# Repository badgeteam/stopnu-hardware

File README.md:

# STOPNU traffic light controller board

## Introduction

The StopNU board is an interface board design to be used with an Heltec V3 board, with purpose to provide a LoRa synchronized traffic light system.
The board has the ability to process inputs from: an Ambient light sensor, 3 button IO channels, a QWIIC interface.
The board can control LED strips via 5V LED control output lines, and using QWIIC peripherals.
IO is also exposed to the 'Expansion connector', which provides a way to breakout IO to future boards.

## Power

The board will be provided 5V power, stabilized outside of the board.
Because the current consumption is limited to 1A, the board it self cannot provide power to LED's controlled by the board.

Even though 3.3V and 5V pins are provided with the expansion header, the total power of these two power railes combined is limited at 3W.

## Pin-out

### Ambient light sensor

The ambient light sensor this circuit is designed for is the [TEPT4400](https://www.vishay.com/docs/81341/tept4400.pdf), where the sensor is connected between the collector and emitter pin.
The current allowed through the sensor results in a voltage that needs to be decoded by the ESP32 micro controller ADC input pin.

The emitter is is connected to ADC pin GPIO02

### LED control outputs

The LED control output pins are level shifted to 5V TTL, in order to work with the WS2812 addressable LED's or compatible.
The pins are output only as the level shifter only works one way.

| LED output | GPIO   |
| ---------- | ------ |
| 1          | GPIO04 |
| 2          | GPIO03 |

### Digital input lines

In order for external input devices to work with the board, 3 input lines have been provided, that are routed through an opto-coupler in order to be more noise resistant.
The IO pins are pulled up to 5V, and need to be pulled down by the input device in order for the board to register an input.

When the pin is pulled down the current through the IO input is 5 mA.

| Button # | GPIO   |
| -------- | ------ |
| 1        | GPIO07 |
| 2        | GPIO06 |
| 3        | GPIO07 |

### QWIIC connector

The QWIIC connector is there to connect external I2C (IIC) sensors and IO modules to the board, providing an extra method of expansion.
The port complies with the pin out and specs as provided by [QWIIC Sparkfun page](https://www.sparkfun.com/qwiic), QWIIC products sold are compatible with this board.

Again for the QWIIC bus 3.3V power supply counts, 3W budget shared with the other peripherals on the board.

| QWIIC pin | GPIO   |
| --------- | -----  |
| SDA       | GPIO34 |
| SCL       | GPIO33 |

### Expansion connector

The expansion connector exposes the Heltec V3 pins useable for IO.
The pins that are connected to the buffered outputs on the bottom of the board are also exposed on the header, but without the buffering.

Please be aware that some pins exposed on the header are used by the Heltec V3 internally, and should be used with care.

Here a list of the Heltec V3 board pins and where they connect to on the expansion header.

| pin | GPIO    | capable        | comments                        |
| --- | ------- | -------------- | ------------------------------- |
| 1   | GND     | Power          |                                 |
| 2   | GND     | Power          |                                 |
| 3   | GPIO41  |                |                                 |
| 4   | GPIO44  |                | Heltec V3 UAR_TX                |
| 5   | GPIO40  |                | Drives Heltec white LED         |
| 6   | GPIO43  |                | Heltec V3 UART_RX               |
| 7   | GPIO39  |                | Heltec V3 external power switch |
| 8   | MCU_RST |                | Heltec V3 Reset pin             |
| 9   | GPIO38  |                | Heltec V3 ADC ctrl              |
| 10  | GPIO00  |                | USER_KEY                        |
| 11  | GPIO01  | ADC            |                                 |
| 12  | GPIO35  |                |                                 |
| 13  | GPIO02  | ADC            |                                 |
| 14  | GPIO34  |                | QWIIC SDA                       |
| 15  | +3.3V   | Power          | 3W max (total)                  |
| 16  | +5V     | Power          | 3W max (total)                  |
| 17  | GND     | Power          |                                 |
| 18  | GND     | Power          |                                 |
| 19  | GPIO03  | ADC            | LED channel 2                   |
| 20  | GPIO45  |                |                                 |
| 21  | GPIO04  | ADC            | LED channel 1                   |
| 22  | GPIO33  |                | QWIIC SCL                       |
| 23  | GPIO05  | ADC            | Button IN 3                     |
| 24  | GPIO46  |                |                                 |
| 25  | GPIO06  | ADC/Input only | Button IN 2                     |
| 26  | GPIO42  |                |
| 27  | GPIO07  | ADC/Input only | Button IN 1                     |
| 28  | GPIO26  |                |                                 |
| 29  | GND     | Power          |                                 |
| 30  | GND     | Power          |                                 |

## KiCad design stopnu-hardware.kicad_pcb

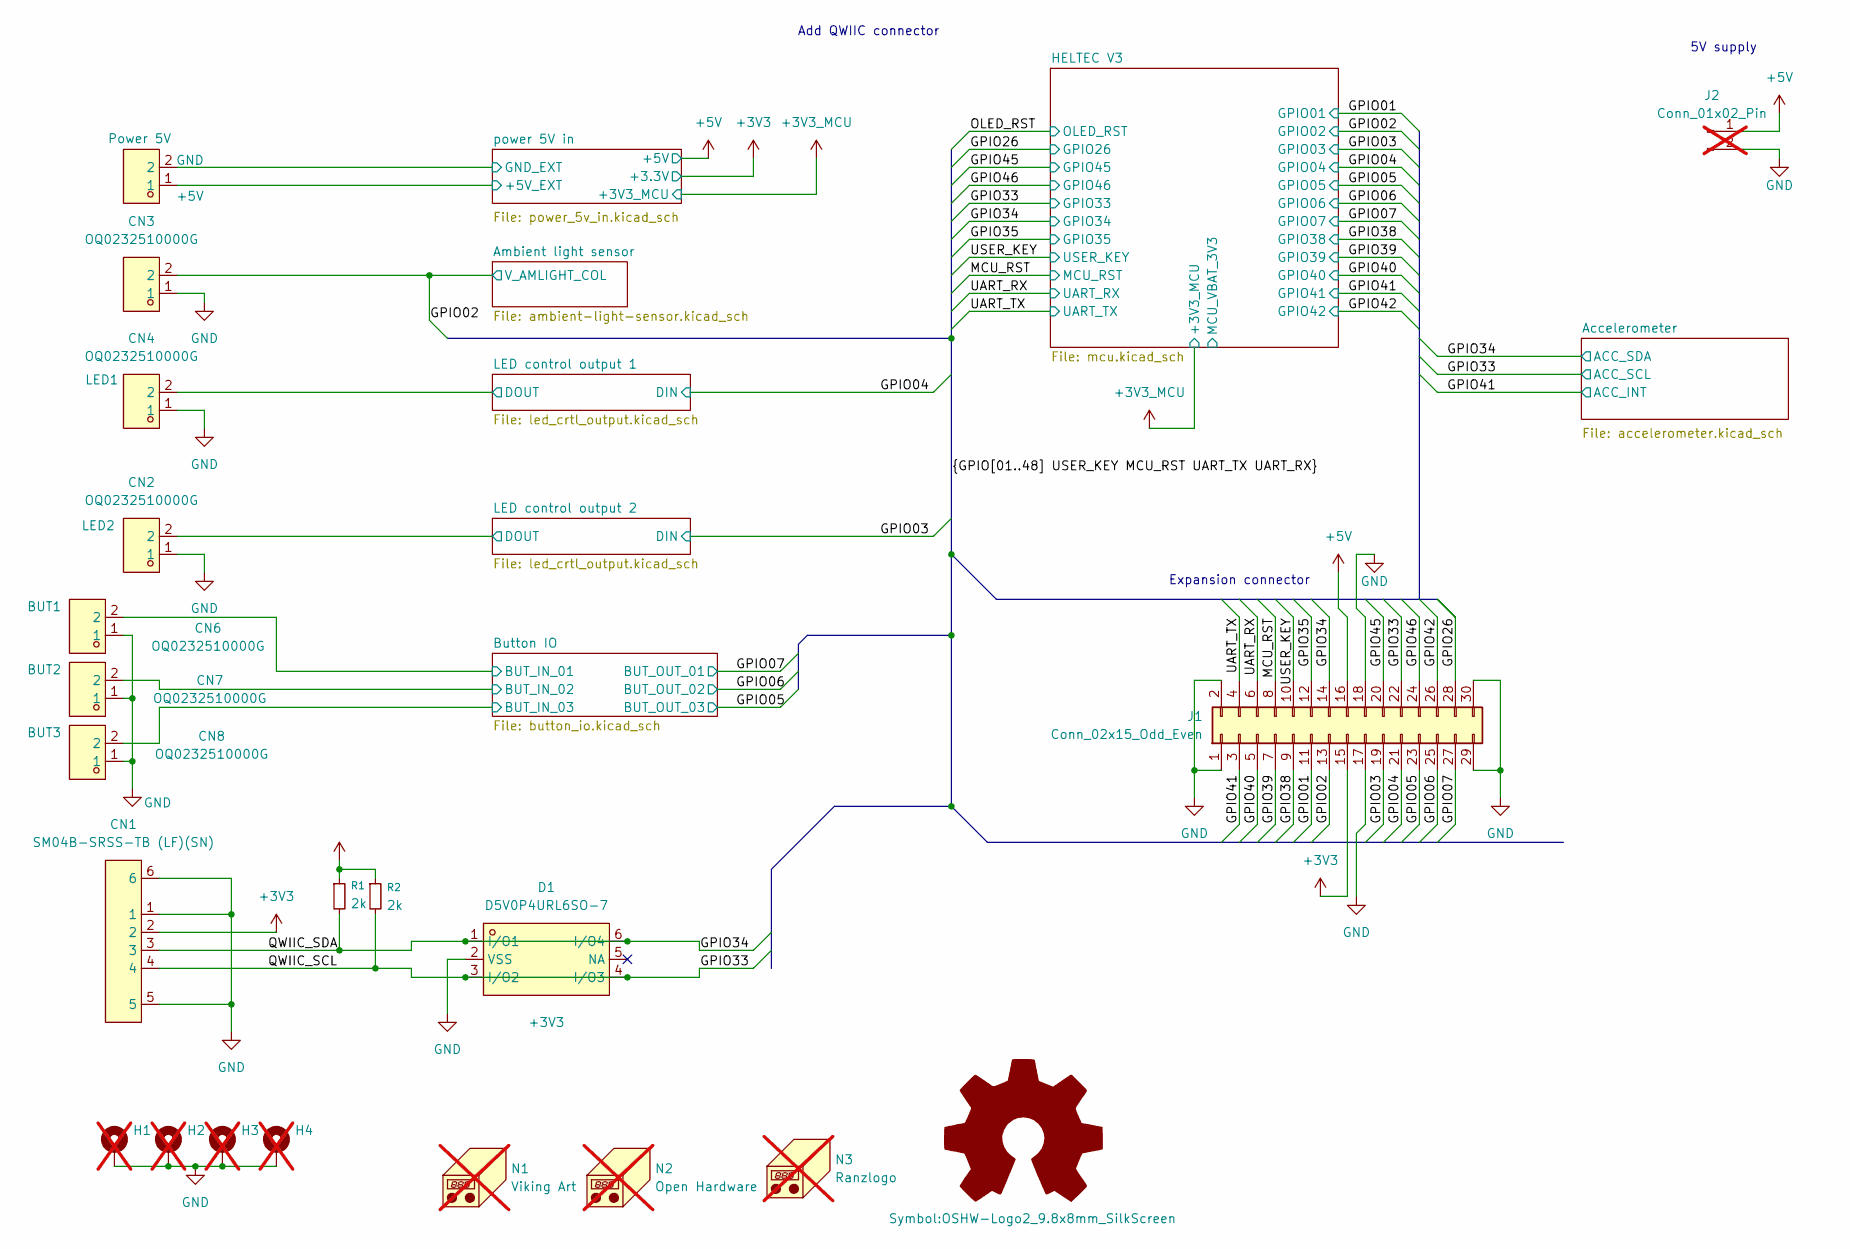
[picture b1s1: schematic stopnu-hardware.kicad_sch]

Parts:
CN1: SM04B-SRSS-TB (LF)(SN); CONN-SMD_4P-P1.00_SM04B-SRSS-TB-LF-SN; LCSC Part C160404
CN2, CN3, CN4, CN5, CN6, CN7, CN8: OQ0232510000G; CONN-TH_OQ0232510000G; LCSC Part C967073
D1: D5V0P4URL6SO-7; SOT-26_L3.0-W1.6-P0.95-LS2.8-BL; LCSC Part C460591
H1, H2, H3, H4: MountingHole_Pad; MountingHole_4.5mm_Pad_Via; not fitted
J1: Conn_02x15_Odd_Even; PinHeader_2x15_P2.54mm_Horizontal; LCSC C2894995
J2: Conn_01x02_Pin; PinHeader_1x02_P2.54mm_Vertical; LCSC C32713268; not fitted
N1: Viking Art; StopNuVikings; not fitted
N2: Open Hardware; OSHW-Logo2_9.8x8mm_SilkScreen; not fitted
N3: Ranzlogo; goatse_01; not fitted
R1, R2: 2k; R_0603_1608Metric; LCSC C22975

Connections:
+3V3: CN1.2, J1.15, R1.1, R2.1; also elsewhere on the board
+5V: J1.16, J2.1; also elsewhere on the board
/Button IO/BUT_IN_01: CN6.2; also elsewhere on the board
/Button IO/BUT_IN_02: CN7.2; also elsewhere on the board
/Button IO/BUT_IN_03: CN8.2; also elsewhere on the board
/GPIO01: J1.11; also elsewhere on the board
/GPIO02: CN3.2, J1.13; also elsewhere on the board
/GPIO03: J1.19; also elsewhere on the board
/GPIO04: J1.21; also elsewhere on the board
/GPIO05: J1.23; also elsewhere on the board
/GPIO06: J1.25; also elsewhere on the board
/GPIO07: J1.27; also elsewhere on the board
/GPIO26: J1.28; also elsewhere on the board
/GPIO33: CN1.4, D1.3 (I/O2), D1.4 (I/O3), J1.22, R2.2; also elsewhere on the board
/GPIO34: CN1.3, D1.1 (I/O1), D1.6 (I/O4), J1.14, R1.2; also elsewhere on the board
/GPIO35: J1.12; also elsewhere on the board
/GPIO38: J1.9; also elsewhere on the board
/GPIO39: J1.7; also elsewhere on the board
/GPIO40: J1.5; also elsewhere on the board
/GPIO41: J1.3; also elsewhere on the board
/GPIO42: J1.26; also elsewhere on the board
/GPIO45: J1.20; also elsewhere on the board
/GPIO46: J1.24; also elsewhere on the board
/LED control output 1/DOUT: CN4.2; also elsewhere on the board
/LED control output 2/DOUT: CN2.2; also elsewhere on the board
/MCU_RST: J1.8; also elsewhere on the board
/UART_RX: J1.6; also elsewhere on the board
/UART_TX: J1.4; also elsewhere on the board
/USER_KEY: J1.10; also elsewhere on the board
/power 5V in/+5V_EXT: CN5.1; also elsewhere on the board
/power 5V in/GND_EXT: CN5.2; also elsewhere on the board
GND: CN1.1, CN1.5, CN1.6, CN2.1, CN3.1, CN4.1, CN6.1, CN7.1, CN8.1, D1.2 (VSS), H1.1, H2.1, H3.1, H4.1, J1.1, J1.2, J1.17, J1.18, J1.29, J1.30, J2.2; also elsewhere on the board

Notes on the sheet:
5V supply
Add QWIIC connector
Expansion connector

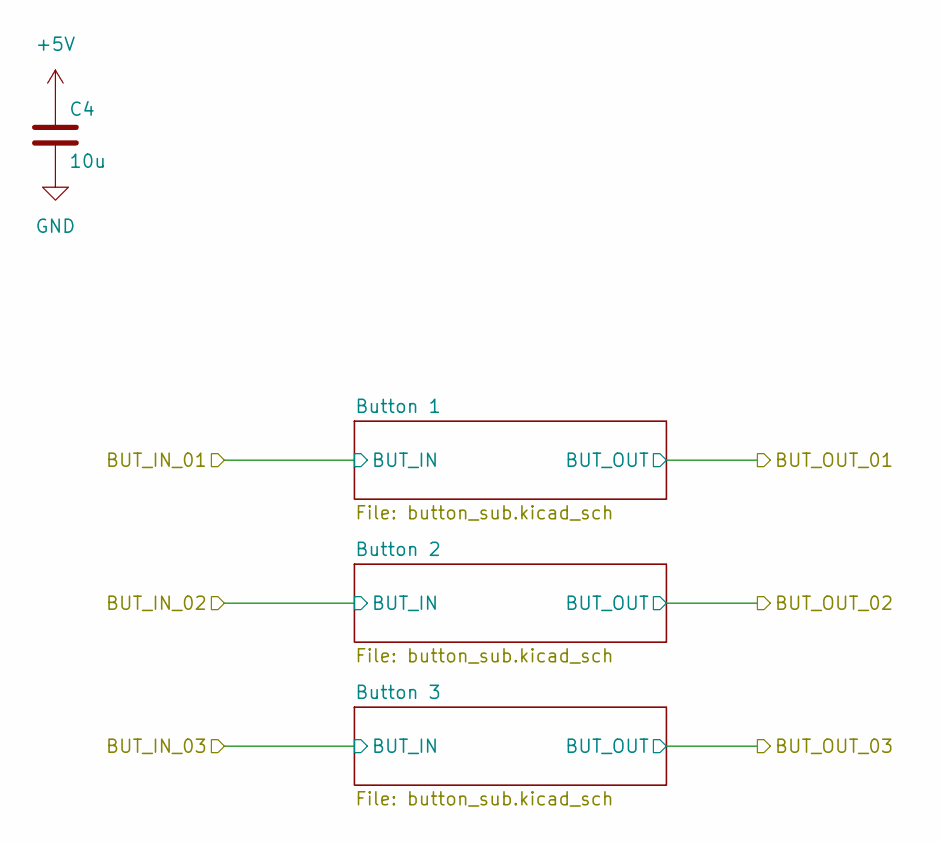
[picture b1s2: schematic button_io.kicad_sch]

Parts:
C4: 10u; C_0805_2012Metric; LCSC C3039694

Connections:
+5V: C4.1; also elsewhere on the board
GND: C4.2; also elsewhere on the board

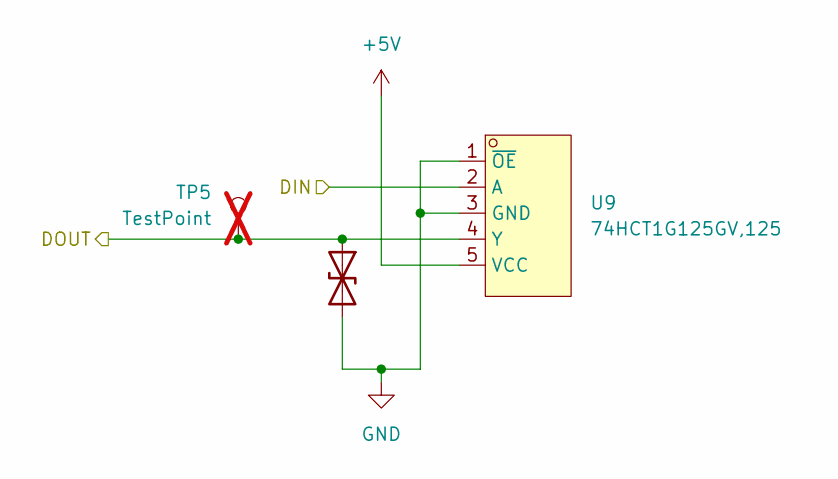
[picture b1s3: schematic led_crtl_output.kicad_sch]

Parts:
D4: ESD prot.; D_SOD-323; LCSC C22363742
TP5: TestPoint; TestPoint_Pad_D1.0mm; not fitted
U9: 74HCT1G125GV,125; SOT-753_L3.1-W1.7-P0.95-LS3.0-BL; LCSC Part C12502

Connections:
+5V: U9.5 (VCC); also elsewhere on the board
/GPIO04: U9.2 (A); also elsewhere on the board
/LED control output 1/DOUT: D4.1 (A1), TP5.1, U9.4 (Y); also elsewhere on the board
GND: D4.2 (A2), U9.1 (~OE), U9.3 (GND); also elsewhere on the board

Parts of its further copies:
D2: ESD prot.; D_SOD-323; LCSC C22363742
TP3: TestPoint; TestPoint_Pad_D1.0mm; not fitted
U10: 74HCT1G125GV,125; SOT-753_L3.1-W1.7-P0.95-LS3.0-BL; LCSC Part C12502

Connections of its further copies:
+5V: U10.5 (VCC); also elsewhere on the board
/GPIO03: U10.2 (A); also elsewhere on the board
/LED control output 2/DOUT: D2.1 (A1), TP3.1, U10.4 (Y); also elsewhere on the board
GND: D2.2 (A2), U10.1 (~OE), U10.3 (GND); also elsewhere on the board

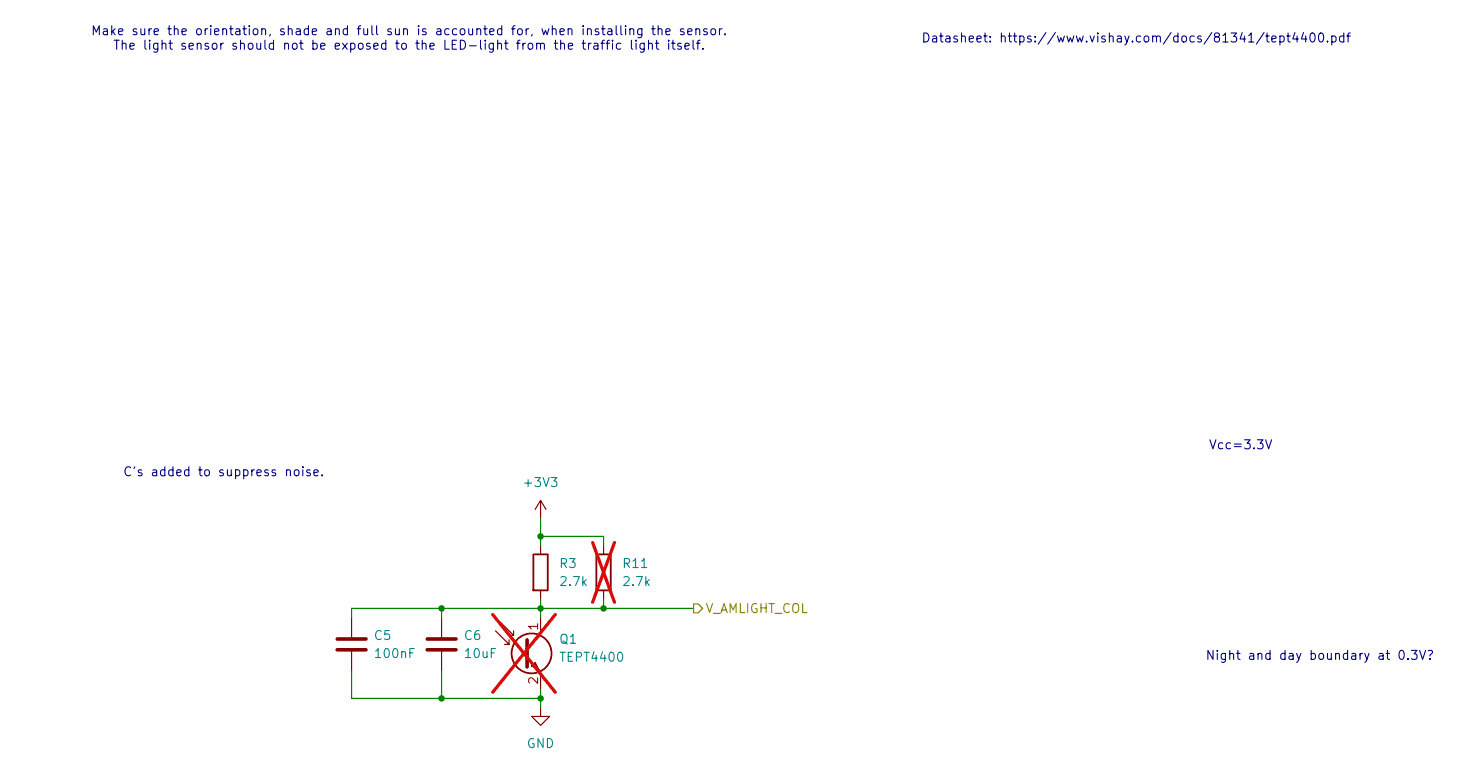
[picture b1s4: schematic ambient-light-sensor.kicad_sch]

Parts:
C5: 100nF; C_0805_2012Metric; LCSC C49678
C6: 10uF; C_0805_2012Metric; LCSC C440198
Q1: TEPT4400; PinHeader_1x02_P1.00mm_Horizontal; not fitted
R3: 2.7k; R_0603_1608Metric; LCSC C13167
R11: 2.7k; R_0603_1608Metric; LCSC C13167; not fitted

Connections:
+3V3: R3.1, R11.1; also elsewhere on the board
/GPIO02: C5.1, C6.1, Q1.1 (C), R3.2, R11.2; also elsewhere on the board
GND: C5.2, C6.2, Q1.2 (E); also elsewhere on the board

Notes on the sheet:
Night and day boundary at 0.3V?
Make sure the orientation, shade and full sun is accounted for, when installing the sensor. The light sensor should not be exposed to the LED-light from the traffic light itself.
Vcc=3.3V
C's added to suppress noise.
Datasheet: https://www.vishay.com/docs/81341/tept4400.pdf

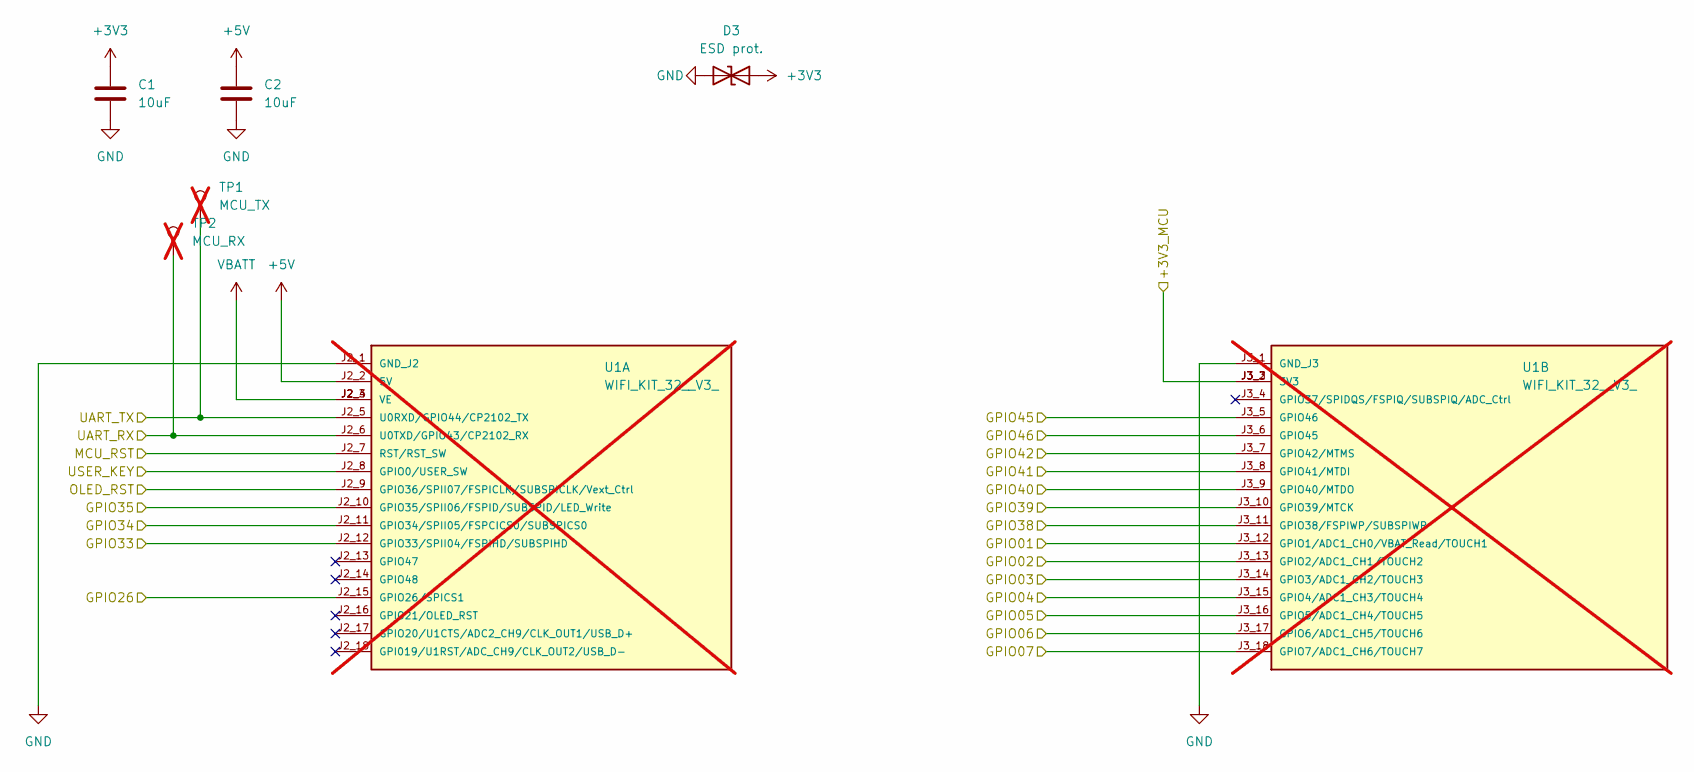
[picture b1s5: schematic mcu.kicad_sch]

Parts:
C1, C2: 10uF; C_0805_2012Metric; LCSC C440198
D3: ESD prot.; D_SOD-323; LCSC C22363742
TP1: MCU_TX; TestPoint_Pad_D1.0mm; not fitted
TP2: MCU_RX; TestPoint_Pad_D1.0mm; not fitted
U1: WIFI_KIT_32__V3_; MODULE_WIFI_KIT_32__V3_; PARTREV Rev 1.1; not fitted

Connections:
+3V3: C1.1, D3.1 (A1); also elsewhere on the board
+3V3_MCU: U1.J3_2 (3V3), U1.J3_3 (3V3); also elsewhere on the board
+5V: C2.1, U1.J2_2 (5V); also elsewhere on the board
/GPIO01: U1.J3_12 (GPIO1/ADC1_CH0/VBAT_Read/TOUCH1); also elsewhere on the board
/GPIO02: U1.J3_13 (GPIO2/ADC1_CH1/TOUCH2); also elsewhere on the board
/GPIO03: U1.J3_14 (GPIO3/ADC1_CH2/TOUCH3); also elsewhere on the board
/GPIO04: U1.J3_15 (GPIO4/ADC1_CH3/TOUCH4); also elsewhere on the board
/GPIO05: U1.J3_16 (GPIO5/ADC1_CH4/TOUCH5); also elsewhere on the board
/GPIO06: U1.J3_17 (GPIO6/ADC1_CH5/TOUCH6); also elsewhere on the board
/GPIO07: U1.J3_18 (GPIO7/ADC1_CH6/TOUCH7); also elsewhere on the board
/GPIO26: U1.J2_15 (GPIO26/SPICS1); also elsewhere on the board
/GPIO33: U1.J2_12 (GPIO33/SPII04/FSPIHD/SUBSPIHD); also elsewhere on the board
/GPIO34: U1.J2_11 (GPIO34/SPII05/FSPCICS0/SUBSPICS0); also elsewhere on the board
/GPIO35: U1.J2_10 (GPIO35/SPII06/FSPID/SUBSPID/LED_Write); also elsewhere on the board
/GPIO38: U1.J3_11 (GPIO38/FSPIWP/SUBSPIWP); also elsewhere on the board
/GPIO39: U1.J3_10 (GPIO39/MTCK); also elsewhere on the board
/GPIO40: U1.J3_9 (GPIO40/MTDO); also elsewhere on the board
/GPIO41: U1.J3_8 (GPIO41/MTDI); also elsewhere on the board
/GPIO42: U1.J3_7 (GPIO42/MTMS); also elsewhere on the board
/GPIO45: U1.J3_5 (GPIO46); also elsewhere on the board
/GPIO46: U1.J3_6 (GPIO45); also elsewhere on the board
/MCU_RST: U1.J2_7 (RST/RST_SW); also elsewhere on the board
/OLED_RST: U1.J2_9 (GPIO36/SPII07/FSPICLK/SUBSPICLK/Vext_Ct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)
/UART_RX: TP2.1, U1.J2_6 (U0TXD/GPIO43/CP2102_RX); also elsewhere on the board
/UART_TX: TP1.1, U1.J2_5 (U0RXD/GPIO44/CP2102_TX); also elsewhere on the board
/USER_KEY: U1.J2_8 (GPIO0/USER_SW); also elsewhere on the board
GND: C1.2, C2.2, D3.2 (A2), U1.J2_1 (GND_J2), U1.J3_1 (GND_J3); also elsewhere on the board
VBATT: U1.J2_3 (VE), U1.J2_4 (VE)

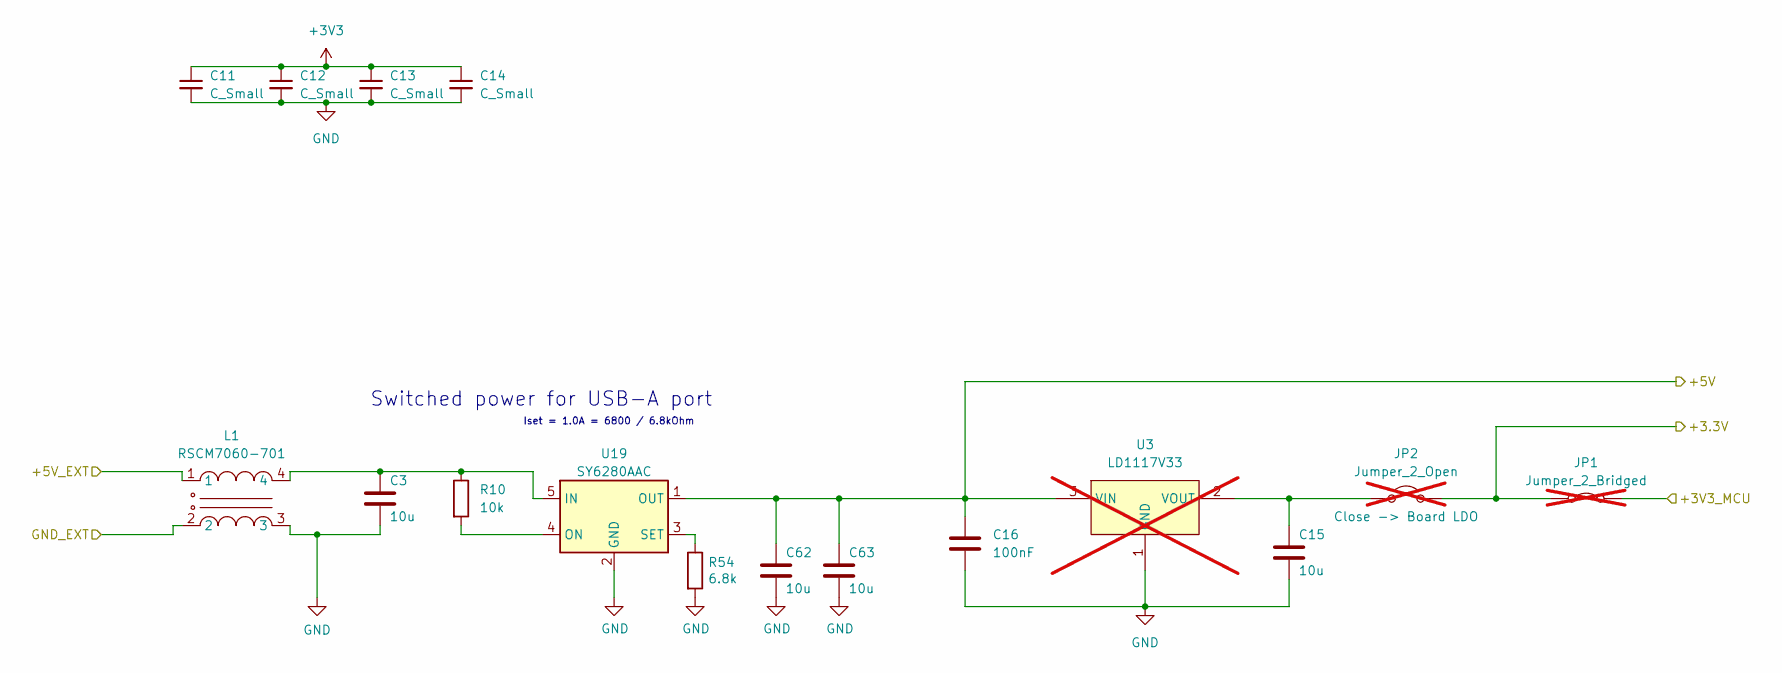
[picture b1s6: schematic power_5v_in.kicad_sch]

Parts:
C3, C15, C62, C63: 10u; C_0805_2012Metric; LCSC C3039694
C11, C12, C13, C14: C_Small; C_0603_1608Metric; LCSC C57112
C16: 100nF; C_0805_2012Metric; LCSC C49678
JP1: Jumper_2_Bridged; SolderJumper-2_P1.3mm_Bridged_RoundedPad1.0x1.5mm; not fitted
JP2: Jumper_2_Open; SolderJumper-2_P1.3mm_Open_RoundedPad1.0x1.5mm; not fitted
L1: RSCM7060-701; FILTER-SMD_4P-L7.0-W6.0-P3.00-TL; LCSC Part C32712963
R10: 10k; R_0603_1608Metric; LCSC C25804
R54: 6.8k; R_0402_1005Metric; LCSC C25917
U3: LD1117V33; TO-220-3_L10.0-W4.5-P2.54-L; LCSC Part C283467; not fitted
U19: SY6280AAC; SOT-23-5; LCSC C55136

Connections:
+3V3: C11.1, C12.1, C13.1, C14.1, JP1.1 (A), JP2.2 (B); also elsewhere on the board
+3V3_MCU: JP1.2 (B); also elsewhere on the board
+5V: C16.1, C62.1, C63.1, U3.3 (VIN), U19.1 (OUT); also elsewhere on the board
/power 5V in/+5V_EXT: L1.1; also elsewhere on the board
/power 5V in/GND_EXT: L1.2; also elsewhere on the board
GND: C3.2, C11.2, C12.2, C13.2, C14.2, C15.2, C16.2, C62.2, C63.2, L1.3, R54.2, U3.1 (GND), U19.2 (GND); also elsewhere on the board
unnamed: C15.1, JP2.1 (A), U3.2 (VOUT)
unnamed: C3.1, L1.4, R10.1, U19.5 (IN)
unnamed: R10.2, U19.4 (ON)
unnamed: R54.1, U19.3 (SET)

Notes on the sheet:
Switched power for USB-A port
Iset = 1.0A = 6800 / 6.8kOhm

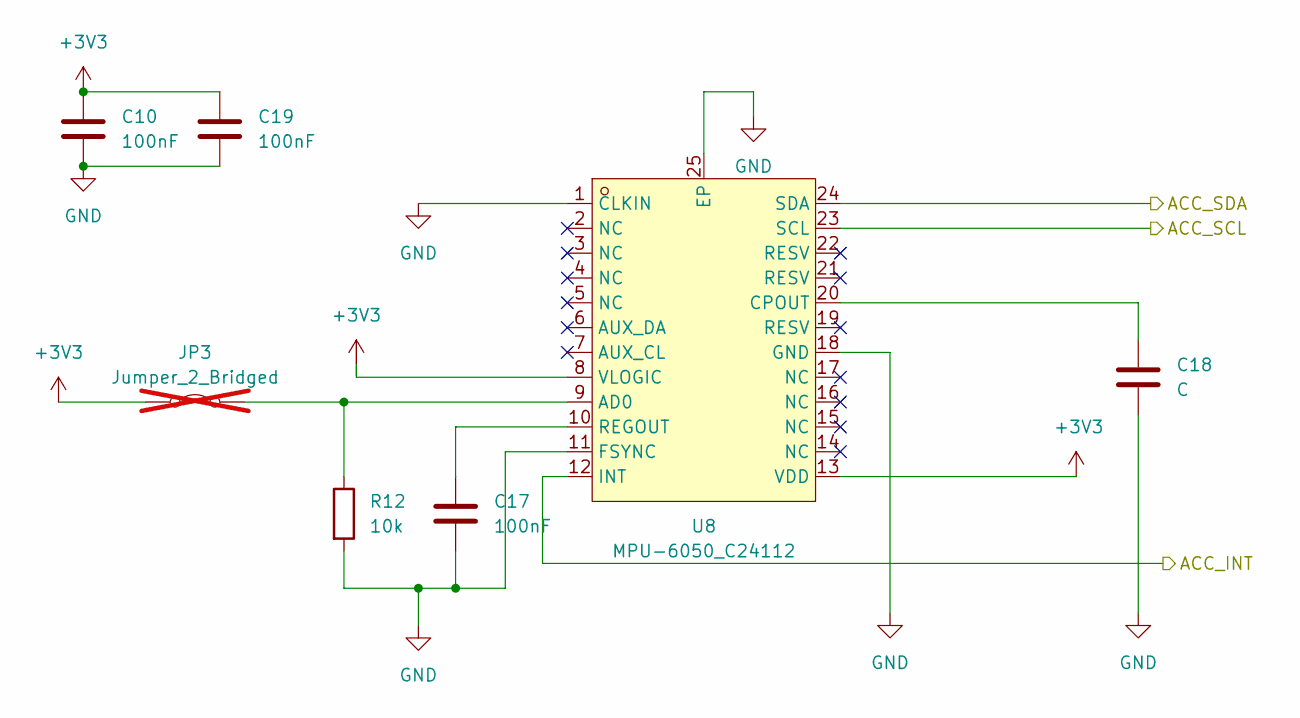
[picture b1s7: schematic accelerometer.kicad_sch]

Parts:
C10, C17, C19: 100nF; C_0805_2012Metric; LCSC C49678
C18: C; C_0603_1608Metric; LCSC C178417
JP3: Jumper_2_Bridged; SolderJumper-2_P1.3mm_Bridged_RoundedPad1.0x1.5mm; not fitted
R12: 10k; R_0603_1608Metric; LCSC C25804
U8: MPU-6050_C24112; QFN-24_L4.0-W4.0-P0.50-BL-EP2.7; LCSC Part C24112

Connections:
+3V3: C10.1, C19.1, JP3.1 (A), U8.8 (VLOGIC), U8.13 (VDD); also elsewhere on the board
/GPIO33: U8.23 (SCL); also elsewhere on the board
/GPIO34: U8.24 (SDA); also elsewhere on the board
/GPIO41: U8.12 (INT); also elsewhere on the board
GND: C10.2, C17.2, C18.2, C19.2, R12.2, U8.1 (CLKIN), U8.11 (FSYNC), U8.18 (GND), U8.25 (EP); also elsewhere on the board
unnamed: JP3.2 (B), R12.1, U8.9 (AD0)
unnamed: C18.1, U8.20 (CPOUT)
unnamed: C17.1, U8.10 (REGOUT)

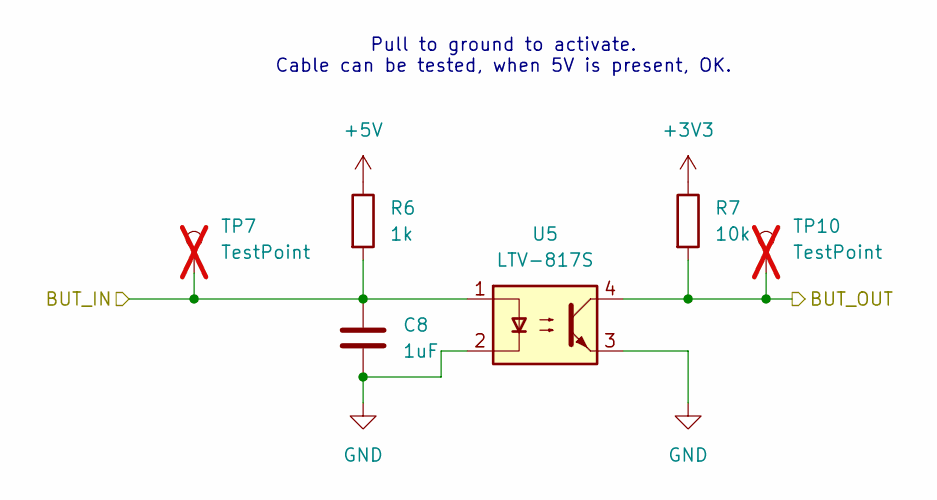
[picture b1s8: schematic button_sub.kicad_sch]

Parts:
C8: 1uF; C_0603_1608Metric; LCSC C15849
R6: 1k; R_0603_1608Metric; LCSC C21190
R7: 10k; R_0603_1608Metric; LCSC C25804
TP7, TP10: TestPoint; TestPoint_Pad_D1.0mm; not fitted
U5: LTV-817S; SMDIP-4_W9.53mm; LCSC C109227

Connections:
+3V3: R7.1; also elsewhere on the board
+5V: R6.1; also elsewhere on the board
/Button IO/BUT_IN_02: C8.1, R6.2, TP7.1, U5.1; also elsewhere on the board
/GPIO06: R7.2, TP10.1, U5.4; also elsewhere on the board
GND: C8.2, U5.2, U5.3; also elsewhere on the board

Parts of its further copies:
C7, C9: 1uF; C_0603_1608Metric; LCSC C15849
R4, R8: 1k; R_0603_1608Metric; LCSC C21190
R5, R9: 10k; R_0603_1608Metric; LCSC C25804
TP8, TP9, TP11, TP12: TestPoint; TestPoint_Pad_D1.0mm; not fitted
U6, U7: LTV-817S; SMDIP-4_W9.53mm; LCSC C109227

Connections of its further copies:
+3V3: R5.1, R9.1; also elsewhere on the board
+5V: R4.1, R8.1; also elsewhere on the board
/Button IO/BUT_IN_01: C7.1, R4.2, TP9.1, U7.1; also elsewhere on the board
/Button IO/BUT_IN_03: C9.1, R8.2, TP8.1, U6.1; also elsewhere on the board
/GPIO05: R9.2, TP11.1, U6.4; also elsewhere on the board
/GPIO07: R5.2, TP12.1, U7.4; also elsewhere on the board
GND: C7.2, C9.2, U6.2, U6.3, U7.2, U7.3; also elsewhere on the board

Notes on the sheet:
Pull to ground to activate. Cable can be tested, when 5V is present, OK.

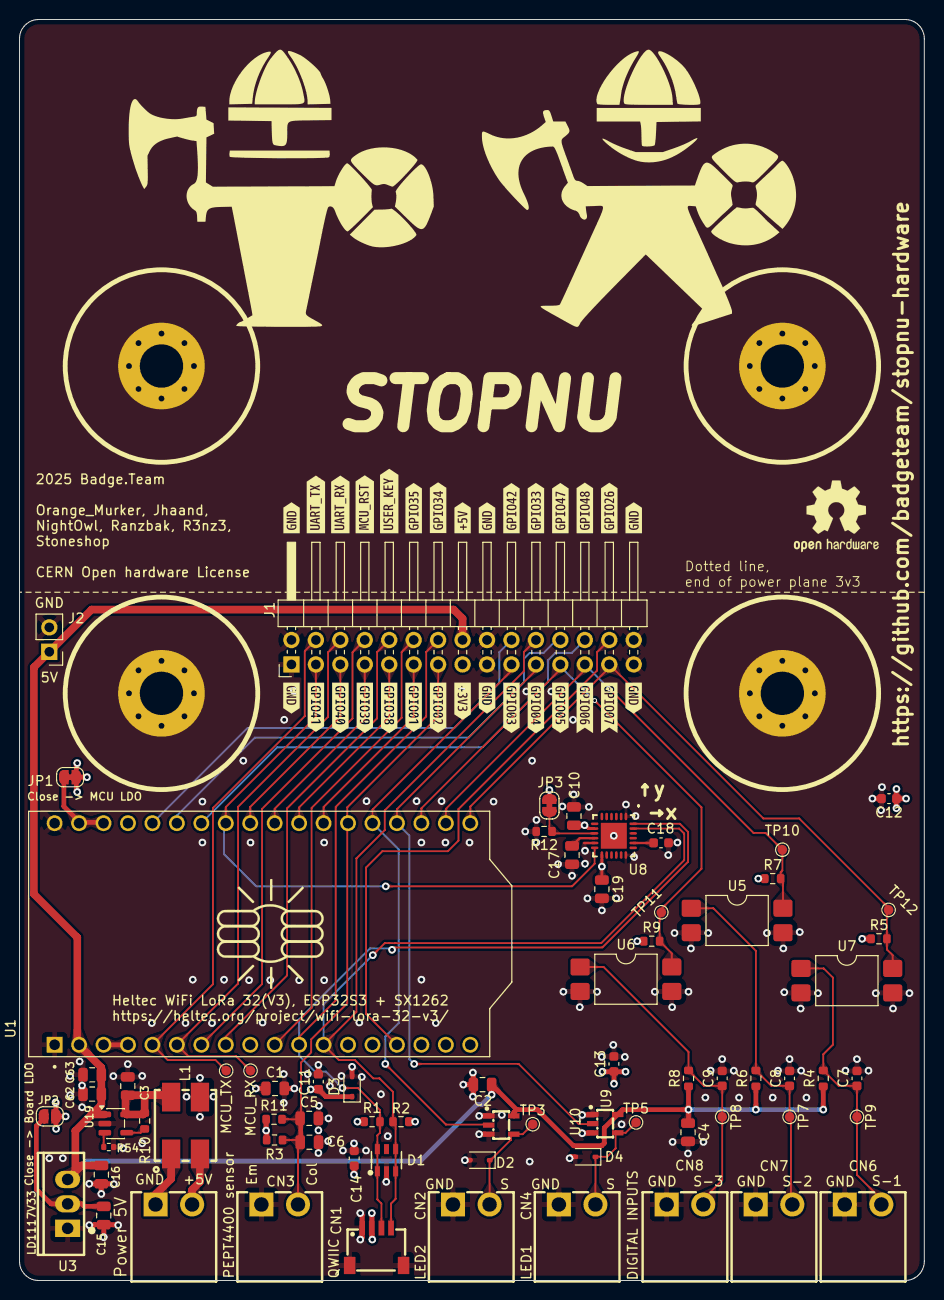
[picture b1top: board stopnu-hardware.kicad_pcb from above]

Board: 4 copper layers, 94.0 x 131.0 mm, 108 parts (0 on the bottom side), 41 nets.

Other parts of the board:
kibuzzard-6946CCA1, kibuzzard-6946CCA1#2, kibuzzard-6946CCA1#3, kibuzzard-6946CCA1#4, kibuzzard-6946CCA1#5, kibuzzard-6946CCA1#6: G***; kibuzzard-6946CCA1
kibuzzard-6946CDDB: G***; kibuzzard-6946CDDB
kibuzzard-6946CE2E: G***; kibuzzard-6946CE2E
kibuzzard-6946CE3C: G***; kibuzzard-6946CE3C
kibuzzard-6946CE4B: G***; kibuzzard-6946CE4B
kibuzzard-6946CE20: G***; kibuzzard-6946CE20
kibuzzard-6946CE89: G***; kibuzzard-6946CE89
kibuzzard-6946CE92: G***; kibuzzard-6946CE92
kibuzzard-6946CE98: G***; kibuzzard-6946CE98
kibuzzard-6946CEA1: G***; kibuzzard-6946CEA1
kibuzzard-6946CEAD: G***; kibuzzard-6946CEAD
kibuzzard-6946CEFA: G***; kibuzzard-6946CEFA
kibuzzard-6946CF2B: G***; kibuzzard-6946CF2B
kibuzzard-6946CF08: G***; kibuzzard-6946CF08
kibuzzard-6946CF12: G***; kibuzzard-6946CF12
kibuzzard-6946CF20: G***; kibuzzard-6946CF20
kibuzzard-6946CF52: G***; kibuzzard-6946CF52
kibuzzard-6946CF89: G***; kibuzzard-6946CF89
kibuzzard-6946CF95: G***; kibuzzard-6946CF95
kibuzzard-6946CFA1: G***; kibuzzard-6946CFA1
kibuzzard-6946CFA8: G***; kibuzzard-6946CFA8
kibuzzard-69470A2F: G***; kibuzzard-69470A2F
kibuzzard-69470A3B: G***; kibuzzard-69470A3B
kibuzzard-69470A66: G***; kibuzzard-69470A66
kibuzzard-69470A71: G***; kibuzzard-69470A71

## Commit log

2025-09-14 First commit very incomplete setup.
2025-09-15 Place opto couplers and some connectors.
2025-09-15 changed driver IC for LED signal to 74HCT1G125GW
2025-09-20 Added input, board square, power, optional LDO.
2025-09-20 Push schematic stuff missed before.
2025-12-16 Some extra work for building the rats nest.
2025-12-17 WIP: Routed version, for first feedback round
2025-12-17 WIP: Added StopNu temp text label.
2025-12-18 Add some vias around GND, STOPNU label
2025-12-18 moved heltec V3 4mm down
2025-12-18 Rotate Optos 90' to handle pcb bending better.
2025-12-18 minor improvements.
2025-12-18 Names of people that contributed.
2025-12-18 Mounting holes to 4.5mm.
2025-12-19 Fixed USB-pin routing, some other cleanups.
2025-12-20 Labeled expansion port, fixed en pin U19 (high)
2025-12-20 Fixed some pinout issues.
2025-12-21 Add README.md, make power input more intuitive in schematic.
2025-12-21 Push, forgot to save.
2025-12-21 Fixed issues + added 3 2 pin connectors for digital (button) inputs.
2025-12-21 Fixed labels 3 digital input channels.
2025-12-21 Changed ambient light sensor to pull-up design.
2025-12-21 Fix D1 3D model, to be placed correctly.
2025-12-21 Changed capacitors to span the TEPT4400
2025-12-21 Power plane not under top of PCB, add 5V to plug in stuff just in case.
2025-12-21 Initial MPU6050 addition.
2025-12-21 Applied rules checker.
2025-12-23 Update viking footprint art.
2026-01-08 Straightened a track between D2 and CN2
2026-01-11 Fixed fabrication files, so PCBA will work with the correct rotation of the components.
2026-01-12 Add orientation mark for accelerometer.
2026-01-15 Fixed issue with too little of a component for second prod run.

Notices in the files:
stopnu-hardware.kicad_pcb:
CERN Open hardware License
